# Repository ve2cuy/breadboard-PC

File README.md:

# breadboard-PC — an 8088 computer on a breadboard

A microcomputer with a PC/XT-inspired architecture, built on solderless breadboards around an
**Intel 8088**. Its ROM, whose source code is **written entirely in 8086 assembly language**, boots
into an interactive menu, runs two BASIC interpreters and **boots PC-DOS 2.1, MS-DOS 3.30, 5.0 and
6.22** from 160 KB to 1.44 MB floppy disk images.

A project by Alain Boudreault (VE2CUY), 2026. *[Version française](README_fr.md)*

<p align="center">
  <br>
  <em>The build: the Black Pill STM32F411 bridge (top centre), the 8088, the 8255, the 8259, the ROM and
  the RAM. The LCD shows the “Information” screen (date and time, versions, RAM, disk, speed).</em>
</p>

## Online simulator

The [Solution-02](Solution-02/) board (stand-alone 8088 / NEC V20, 512 KB, 20×4 LCD, LEDs, PS/2 keyboard,
software UART, SD card) also runs in the browser, emulated in Rust/WebAssembly with its real BIOS:
**[launch the simulator](https://ve2cuy.github.io/breadboard-PC/)** (English and French). PCB view with live pin levels, oscilloscope,
32-channel logic analyzer with protocol decoders, debugger, fault injection.

<p align="center">
  <br>
  <em>The simulator running PC-DOS 2.1 (DIR typed on the PS/2 keyboard). Click the animation to open the simulator.
  More in the <a href="Solution-02/Simulateur/README.md">simulator README</a>.</em>
</p>

**New: [the simulator with the Pico W](https://ve2cuy.github.io/breadboard-PC/pico/)** — the current board (2026-11-23):
- the ATmega328P terminal;
- a Raspberry Pi Pico W on ports 50h-57h behind two SN74LVC245, with READY wait states;
- BIOS 3.3, which reads the SD card through the Pico;
- **TCP/IP and the Internet** from DOS (mTCP) and ELKS, through the Pico's real firmware core: DNS-over-HTTPS, HTTP,
  and real TCP with a small local relay.

Details in the [Simulateur-Pico README](Solution-02/Simulateur-Pico/README.md) and the [Pico README](Solution-02/pico/README.md).

## At a glance

| | |
|---|---|
| **Processor** | Intel 8088, 4.77 MHz by default, adjustable from 1 to 10 MHz (tested up to 7.38 MHz) |
| **Memory** | 256 KB ROM (W29C020C, `C0000h`–`FFFFFh`); **512 KB** static RAM (AS6C4008, `00000h`–`7FFFFh`), 510 KB of it for DOS |
| **I/O** | 8255A in mode 2 (bus to the bridge), 8259A (interrupts), 4×20 I2C LCD, PS/2 keyboard |
| **Bridge** | WeAct **Black Pill STM32F411** board (firmware 1.6): keyboard, USB terminal, LCD, clock, disk, RESET |
| **Software** | ROM written entirely in assembly (NASM, strict 8086 instruction set): menu, BIOS for DOS, Tiny BASIC, GW-BASIC-style BASIC, RAM test with a memory map |
| **Operating systems** | PC-DOS 2.1, MS-DOS 3.30, 5.0 and 6.22, booted from a floppy disk image (160 KB to 1.44 MB) |

## The build

The core of the machine (processor, address latches, data buffer, ROM, RAM, decoding) is wired on
breadboards with 74LS/74HC logic and no programmable logic (no GAL, no CPLD):

- two **74LS373** latch `A0`–`A7` and `A16`–`A19` on `ALE`; a **74HC245** buffers `D0`–`D7`
  (`DEN`, `DT/R`);
- two **74LS00** do all the decoding, with `M` = memory cycle (`IO/M` = 0):
  - **ROM**: `CE# = NAND(A19, M)` — `C0000h`–`FFFFFh`;
  - **RAM**: `CE# = NAND(/A19, M)` — `00000h`–`7FFFFh`;
  - **8255** (ports `80h`–`83h`): `CS# = NAND(IO, A7)`;
  - **8259** (ports `20h`–`21h`): `CS# = NAND(IO, A5)`;
- the 8088's `RD#` and `WR#` go straight to the ROM, the RAM, the 8255 and the 8259.

<p align="center">
  <br>
  <em>Schematic of the build (KiCad, <a href="kicad/Breadboard-pc">kicad/Breadboard-pc</a>). The clock comes from the
  bridge (<code>CLK_STM</code>) or from an external input, selected by jumper JP1. On the PCB, a third 74LS373 (U12)
  also latches A8-A11, so the whole address bus (A0-A19) can drive two 10-LED bargraphs (readable when single-stepping or halted); J5 brings the bus
  out on a 2 x 20 header.</em>
</p>

<p align="center">
  <br>
  <em>PCB v2 (120 x 124.2 mm, 2 layers), KiCad 3D render: 8088, ZIF socket for the ROM, Black Pill bridge (U5),
  512 KB RAM, 8255, 8259, address bargraphs and J5 bus connector. Routed with Freerouting.</em>
</p>

### The signals in action

The animation follows the machine from RESET to DOS reading a sector: the reset vector fetched from
ROM, a RAM write, programming the 8259 and the interrupt vector table (IVT), a key press and the `IRQ1`
interrupt, a BIOS call (`INT 13h`) and the bridge's burst reply. For each step: the chips involved, the
level of the control signals and the memory area targeted.

The animation is generated by [medias/animation/generer_signaux.py](medias/animation/generer_signaux.py).

## The circuit

The 8088 does not bit-bang any peripheral. All traffic goes through **a single 8255 in mode 2**: an
8-bit bidirectional bus with hardware handshaking, connected to the bridge. Every byte received from
the bridge raises an interrupt (`IR1` of the 8259); during a bridge command, `IR1` is masked and the
BIOS polls for the replies.

```mermaid
flowchart LR
    CPU["Intel 8088"] --- BUS(("Bus<br>A0-A19 / D0-D7"))
    BUS --- ROM["256 KB ROM<br>W29C020C"]
    BUS --- RAM["512 KB RAM<br>AS6C4008"]
    BUS --- PIO["8255A<br>mode 2"]
    BUS --- PIC["8259A"]
    PIO -- "INTR → IR1" --> PIC
    PIC -- INTR --> CPU
    PIO <== "Port A (8 bits) + handshake" ==> BRIDGE["Bridge<br>Black Pill STM32F411"]
    BRIDGE -- "CLK, RESET" --> CPU
    KBD["PS/2 keyboard"] --> BRIDGE
    BRIDGE <-- "USB (serial + drive)" --> PC["PC: terminal"]
    BRIDGE --> LCD["4×20 I2C LCD"]
    BRIDGE --- FLASH["8 MB flash<br>FAT16"]
```

The bridge wiring in detail (pins, 3.3 V / 5 V levels, pull-up resistors) is described (in French) in
[arduino/8088_bridge_stm32/README.md](arduino/8088_bridge_stm32/README.md).

## The STM32 bridge

The bridge firmware (a PlatformIO project, [arduino/8088_bridge_stm32](arduino/8088_bridge_stm32))
gives the 8088 the peripherals of a PC:

| Function | Details |
|---|---|
| **PS/2 keyboard** | Frame decoding; raw scan codes passed to the 8088 |
| **Terminal** | Native USB serial port to the PC (ANSI, 80 columns, UTF-8) |
| **Display** | 4×20 HD44780 LCD over I2C (PCF8574) |
| **Real-time clock** | STM32 RTC (32.768 kHz crystal): `TIME$`, `DATE$`, `INT 1Ah` |
| **Disk** | 8 MB W25Q64 SPI flash formatted FAT16: files, sectors, floppy images mounted as A: (read-only ones too) |
| **Throughput** | Replies sent **in bursts**, as soon as the 8088 has read the previous byte (firmware 1.6) |
| **USB drive** | The flash is exposed to the PC as a USB drive (`USB ON` / `USB OFF`) to copy files onto it |
| **8088 clock** | `CLK` signal generated by hardware PWM, 1 to 10 MHz |
| **8088 RESET** | Held while the bridge starts up; **Ctrl-Alt-Del** (PS/2) or **Ctrl-\\** (terminal) |

The 8088 talks to the bridge through a command protocol on a dedicated channel
(see [Solution-01/lib/bridge.asm](Solution-01/lib/bridge.asm)). The firmware is flashed over USB, with
the board in DFU mode: `platformio run -e blackpill_f411ce_usbdrive -t upload`.

## The menu

At power-up, the ROM displays a menu on both the terminal and the LCD. It can be driven from either
the PS/2 keyboard or the terminal; **Esc** goes back to the previous menu.

| Menu | Options |
|---|---|
| **1) Basic** | Tiny BASIC; GW-BASIC-style BASIC |
| **2) Memory functions** | Memory dump and editing, CPU registers, code entry and execution, interrupt vector table; **RAM test**: *Trace* (full progress), *MAP* (memory map and summary only) or *Loop* (MAP repeated until Esc) |
| **3) USB Disk** | USB drive toggle, file list, **booting a disk image** |
| **4) Configuration** | Clock speed (0.1 and 1 MHz steps; 2.35, 4.77, 8 and 7.2 MHz presets), CPU speed test, date and time, information screen |

The **RAM test** checks all 512 KB byte by byte (the test stack is moved to low RAM, the last 2 KB are
tested separately), then the address lines `A0`–`A18` (the chip's real capacity). It ends with a
**memory map** (one character per KB) and the good and faulty amounts.

## BASIC

An original reimplementation inspired by GW-BASIC: same keywords, same error messages, integers,
single-precision floating point (in software) and strings. About 54 KB are free for programs.

| Category | Commands and functions |
|---|---|
| **Program** | `RUN` `LIST` `EDIT` `DELETE` `NEW` `CLEAR` `CONT` `TRON` `TROFF` `HELP` `SYSTEM` |
| **Control flow** | `IF…THEN…ELSE` `GOTO` `GOSUB`/`RETURN` `ON…GOTO/GOSUB` `FOR…NEXT` `WHILE…WEND` `END` `STOP` |
| **Data** | `LET` `DIM` `ERASE` `SWAP` `DATA`/`READ`/`RESTORE` `DEF FN` `DEFINT`/`DEFSNG`/`DEFSTR` |
| **Input/output** | `PRINT` `INPUT` `LINE INPUT` `INKEY$` `CLS` `LOCATE` `COLOR` `BEEP` |
| **Math** | `ABS` `SGN` `INT` `FIX` `SQR` `SIN` `COS` `TAN` `ATN` `LOG` `EXP` `RND` `RANDOMIZE` |
| **Strings** | `LEN` `LEFT$` `RIGHT$` `MID$` `INSTR` `CHR$` `ASC` `STR$` `VAL` `HEX$` `UCASE$` `STRING$` |
| **Files** | `SAVE` `LOAD` `MERGE` `FILES` `KILL` `FORMAT`; `OPEN` `PRINT #` `INPUT #` `EOF` `CLOSE` |
| **Clock** | `TIMER` `TIME$` `DATE$` (read and set the bridge RTC) |
| **Machine** | `PEEK` `POKE` `DEF SEG` `INP` `OUT` `WAIT` `CALL` `FRE` |
| **Disk and system** | `DSKREAD` `DSKWRITE` `USB ON`/`OFF` `BOOT "image.img"` |

## DOS 2.1 to 6.22

The ROM provides the BIOS layer a DOS expects: disk (`INT 13h`, CHS and LBA), keyboard (`INT 16h`),
clock (`INT 1Ah`), text output to the terminal (`INT 10h`) and bootstrap (`INT 19h`). A floppy image
copied to the flash (through the USB drive) is mounted as drive **A:** and booted from
**USB Disk → 3) Boot disk image**, or with `BOOT "PCDOS2_1.IMG"` from BASIC. DOS writes go to the
image file; a read-only image is mounted anyway, without write access.

<p align="center">
  <br>
  <em>PC-DOS 2.1: booting from the image (one dot per sector read), VER, DIR /W</em>
</p>

<p align="center">
  <br>
  <em>MS-DOS 3.30</em>
</p>

What makes DOS 5.0 and 6.22 possible:

- **512 KB of RAM** (these versions require at least 256 KB);
- the **model byte** `FEh` (PC/XT) at `F000:FFFE`: without it, DOS 5 takes the AT keyboard path
  (ports `60h`/`64h`), which hits the 8259 with this decoding;
- the BIOS tick counter `0040:006C`, kept in step with the bridge clock (there is no timer on this
  build): DOS 6 times its F5/F8 boot pause with it;
- **1.44 MB** floppies (geometry from the image size, `INT 13h AH=08h/18h`).

DOS accented letters and box-drawing characters (code page 437) are converted to **UTF-8** on the
terminal: the PC terminal must be set to UTF-8.

Limitations: no video hardware (programs that write to video memory display nothing); DOS keyboard
input from the terminal only; **KEYB** does not work (it reads the keyboard through port `60h`) —
setup disks that start it from `AUTOEXEC.BAT` must have it removed (see the `-nokeyb` copies in
[PC-DOS/](PC-DOS)).

## Building the ROM

```sh
cd Solution-01
make            # solution-01.bin (256 KB, 512 KB RAM); make rom-en for English; make rom-128: 128 KB RAM
make check      # checks size, reset vector, signature and model byte
make test       # test benches under emulation (Unicorn)
make test-rom   # full ROM simulation: DOS, BASIC, PS/2 keyboard
```

Tools: NASM, GNU Make, Python 3 (+ `unicorn` for the tests); PlatformIO for the bridge.

## Repository layout

| Folder | Contents |
|---|---|
| [Solution-01/](Solution-01) | 8088 ROM (NASM) and tests; full technical documentation (in French) in [Solution-01/README.md](Solution-01/README.md) |
| [arduino/8088_bridge_stm32/](arduino/8088_bridge_stm32) | Firmware of the Black Pill STM32F411 bridge (PlatformIO) |
| [kicad/](kicad) | Schematic and PCB of the build |
| [PC-DOS/](PC-DOS) | Test floppy disk images |
| [medias/](medias) | Datasheets, schematic, PCB render, signal animation and screenshots |

> The terminal screenshots on this page are produced by the actual (English) ROM, running in the
> project's simulator ([medias/captures/generer.py](medias/captures/generer.py)).

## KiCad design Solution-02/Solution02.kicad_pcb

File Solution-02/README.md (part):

# Solution-02 — stand-alone 8088 / NEC V20 computer (VE2CUY)

*[Version française](README_fr.md)*

An 8088 (or NEC V20) computer built on a breadboard, **without the STM32 bridge**:
the processor drives its LCD and its memory directly.

- Clock: 82C84 + 16 MHz crystal → **5.33 MHz** (16 / 3)
- ROM: 29C020 (W29C020C), 256 KB
- RAM: HM628512, 512 KB
- Address latches: 2 × 74HC573 (U2: A0–A7, U3: A16–A19)
- Decoding: 74LS00 (U5), 74LS138 (U8), 74LS02 (U9)
- Display: 20×4 LCD (HD44780 / ST7066U), 8-bit bus, write only
- Parallel I/O: 8255 (U7, µPD71055C) at 10h–13h, 24 LEDs on J1–J3
- Keyboard and UART: second 8255 (U12) at 30h–33h — PS/2 keyboard (USB-A socket J4) and
  9600 8N1 software UART (J5), bit-banged as in Solution-01
- **PC-DOS 2.1 in ROM**: the 180 KB floppy is in the ROM (drive A:, read only); IBM PC-style
  BIOS (INT 10h, 13h, 16h…) through software interrupts, 24 × 80 DOS screen seen through a
  20 × 4 window on the LCD

Schematic: [Solution02.kicad_sch](Solution02.kicad_sch).
PCB: [Solution02.kicad_pcb](Solution02.kicad_pcb) (172 × 100 mm, 2 layers; see [PCB](#pcb)).
Log of the steps: [Directives.md](Directives.md) (French).

<p align="center">
  <br>
  <em>Solution-02 schematic (click to enlarge).</em>
</p>

## Memory map

| Addresses | Contents | Selection |
|---|---|---|
| 00000h–7FFFFh | 512 KB RAM | CE# = NAND(/A19, M) — U5 pin 8 |
| 80000h–FFFFFh | 256 KB ROM | CE# = NAND(A19, M) — U5 pin 6 |

A18 is not connected to the ROM: the 256 KB image appears twice
(80000h–BFFFFh and C0000h–FFFFFh). The BIOS occupies the last 64 KB of the
image (offset 30000h), seen at **F000:0000**. At reset, the 8088 starts
at FFFF:0000 = FFFF0h = F000:FFF0 (offset 3FFF0h of the image), where there is
a `JMP F000:0000`.

ROM and RAM contents with BIOS 2.3:

| Addresses | Contents |
|---|---|
| 00000h–003FFh | interrupt vector table (filled by "Load DOS") |
| 00400h–004FFh | BIOS data area (BDA): equipment, memory, video mode |
| 00500h–5EBFFh | DOS and programs (**379 KB** reported by INT 12h; **507 KB** when B: is the card's DOS 2.1 image) |
| 5EC00h–5EFFFh | private INT 10h stack (1 KB, BIOS 2.5; at 7EC00h–7EFFFh when DOS gets 507 KB) |
| 10000h–1FFFFh | (outside DOS) **BASIC** segment (menu 6): program, variables, stack |
| 5F000h–7EFFFh | **drive B:**: 128 KB virtual disk (kept after Ctrl + Alt + Del) |
| 7F000h–7FFFFh | BIOS data (DSEG = 7F00h): 24 × 80 screen, variables, queues, LCD copy, animation stack (900h–AFFh), menu stack |
| C0000h–ECFFFh | **reduced PC-DOS 2.1 floppy** (180 KB: 40 cylinders, 1 head, 9 sectors) = offset 0 of the image |
| ED000h–EFFFFh | free (FFh) |
| F0000h–F7FFFh | BIOS |
| F8000h–FFFEFh | **BASIC** (basic_s02.asm: the Solution-01 BASIC, ~25 KB) |
| FFFF0h | RESET |

The ROM's PGM (WE#) pin is tied to +5 V: a write by DOS or a program into the
ROM area (for instance at B8000h, a PC's video memory) has no effect.

## I/O ports (74LS138, U8)

U8 decodes **A7 = 0**, **IO/M = 1** (E1# = E2# = A7, E3 = IO/M) and
**A6–A4** (inputs A, B, C). Each active-low output covers a block of 16 ports:

| Output | U8 pin | Ports | Use |
|---|---|---|---|
| O0 | 15 | 00h–0Fh | **LCD (in use)**: 00h = command, 01h = data (RS = A0) |
| O1 | 14 | 10h–1Fh | **8255 (U7, in use)**: 10h = PA, 11h = PB, 12h = PC, 13h = control (A0–A1) |
| O2 | 13 | 20h–2Fh | **8259A (U13)**: 20h = ICW1/OCW2/OCW3 (A0 = 0), 21h = ICW2-4/OCW1 (mask) — as on the PC |
| O3 | 12 | 30h–3Fh | **second 8255 (U12, in use)**: 30h = PA, 31h = PB, 32h = PC, 33h = control (keyboard, software UART, SD reader) |
| O4 | 11 | 40h–4Fh | **8253-2 (U15)**: 40h–42h = counters 0–2, 43h = mode (A0–A1) |
| O5 | 10 | 50h–5Fh | free |
| O6 | 9 | 60h–6Fh | **port 61h latch (U16)**: bit 0 = GATE2, bit 1 = speaker (write only) |
| O7 | 7 | 70h–7Fh | free |

Good to know:

- **A0–A3 do not go through the 138.** They go directly to the peripheral to
  select its registers. A peripheral that only uses a few of them, such as an
  8255 (A0–A1), appears several times in its block: 60h–63h, then 64h–67h, etc.
- **A8–A15 are not decoded.** With `IN/OUT port, AL` (8-bit port), they are 0.
  With `IN/OUT DX`, each block repeats every 256 ports.
- **Ports 80h–FFh (A7 = 1) are not decoded.** A second 138 enabled by A7 = 1
  and IO/M = 1 would provide 8 more blocks.
- **No RD#/WR# in the 138.** Its outputs depend only on the address. They suit
  as is the CS# of chips that receive RD# and WR# separately (8255, 8253, 8259,
  16550…). For a simple latch (74LS374/573) or a buffer (74LS244), the output
  must be combined with WR# or RD#, as for the LCD: E = NOR(WR#, O0) (U9), and
  the port 61h latch: clock = OR(WR#, O6) (U9). All 4 NOR gates of U9 are used.
- The decoding falls on the same blocks as a PC/XT: an 8259 on O2, an 8253 on
  O4 and an 8255 on O6 would be at the standard addresses (20h, 40h, 60h),
  which will make a compatible BIOS easier.

## 20×4 LCD

- Data bus DB0–DB7 connected directly to AD0–AD7 of the 8088.
- RS = A0 (latched by U2), E = NOR(WR#, O0) (U9 pin 13).
- R/W tied to ground: the busy flag cannot be read, each write is followed by
  a software delay.
- Contrast set by RV1 (VO pin).
- The E pulse lasts about 2 cycles (≈ 375 ns at 5.33 MHz): enough for an
  HD44780U (230 ns minimum), to watch with a slower controller.

## 8255 (U7) and LEDs

CMOS 8255 (µPD71055C) selected by **O1** of the 74LS138: ports **10h–13h**
(repeated up to 1Fh, since only A0–A1 go to the 8255).

| 8255 pin | Signal | Comes from |
|---|---|---|
| 34, 33, 32, 31, 30, 29, 28, 27 | D0–D7 | AD0–AD7 of the 8088 |
| 9, 8 | A0, A1 | U2 (74HC573) Q0, Q1 |
| 6 | CS# | U8 (74LS138) pin 14 (O1) |
| 5 | RD# | RD# (8088 pin 32) |
| 36 | WR# | WR# (8088 pin 29) |
| 35 | RESET | 82C84 RESET (U11 pin 10, 8088 pin 21) |
| 26 / 7 | VCC / GND | +5 V / GND (+ 100 nF) |
| 4, 3, 2, 1, 40, 39, 38, 37 | PA0–PA7 | J1 pins 1–8 |
| 18–25 | PB0–PB7 | J2 pins 1–8 |
| 14, 15, 16, 17, 13, 12, 11, 10 | PC0–PC7 | J3 pins 1–8 |

J1, J2 and J3 (1×10): pins 1–8 = PA/PB/PC 0–7, pin 9 = +5 V, pin 10 = GND.

LEDs: an output at 1 lights the LED if it is wired **output → 1 kΩ → anode,
cathode → GND** (pin 10). The 82C55 only supplies ~2.5 mA per output: for
brighter LEDs, go through a ULN2803 or a 74HC245.

**Bar graphs** (as in Solution-01): three HDSP-4830 (BAR1–BAR3) in parallel
with J1–J3, wired as a **contiguous chain of 30 LEDs**, like the address lines
of Solution-01: anode on the 8255 output, cathode to ground through **390 Ω** —
segments 1 to 9 through a network of 9 bussed resistors (RN1–RN3, SIP10),
segment 10 through a single resistor (R5–R7).

| Bar graph | Anode pins 1 → 10 | Cathodes |
|---|---|---|
| BAR1 | 1–6 free (bits 24–29), 7–10 = PC7 → PC4 | RN1 + R5 |
| BAR2 | PC3 → PC0, PA7 → PA2 | RN2 + R6 |
| BAR3 | PA1, PA0, PB7 → PB0 | RN3 + R7 |

Bit 0 (PB0) = pin 10 of BAR3, bit 23 (PC7) = pin 7 of BAR1: laid out from left
to right (BAR1, BAR2, BAR3, pin 1 on the left), the bar graphs show the BIOS
row (PC7 … PB0) with the 6 most significant LEDs off on the left. The current
is limited by the 82C55 output (~2.5 mA) rather than by the 390 Ω.

At RESET, the 8255 sets its 3 ports as inputs (floating outputs). The BIOS
sends control word **80h** (mode 0, PA, PB and PC as outputs) and turns the
LEDs off right at startup, just after initializing the LCD.

## 8253 (U15): timer

**NEC D8253C-2** (clock up to **5 MHz**) selected by **O4** of the 74LS138:
ports **40h–43h**, as on the PC (repeated up to 4Fh). The clock is PCLK of the
82C84 (16 MHz / 6 = **2.67 MHz**): an 8253-2 (5 MHz) or an 8254 (8 MHz) is
required; an ordinary 8253 or 8253-5 is limited to 2.6 MHz. In the schematic,
the symbol is the 82C54's (same pinout). The BIOS only uses what all these
chips have: mode 3 and counter latch (word 00h).

| 8253 pin | Signal | Comes from / goes to |
|---|---|---|
| 8 → 1 | D0 → D7 | AD0–AD7 of the 8088 |
| 19, 20 | A0, A1 | U2 (74HC573) Q0, Q1 |
| 21 | CS# | U8 (74LS138) pin 11 (O4) |
| 22 / 23 | RD# / WR# | 8088 pins 32 / 29 |
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
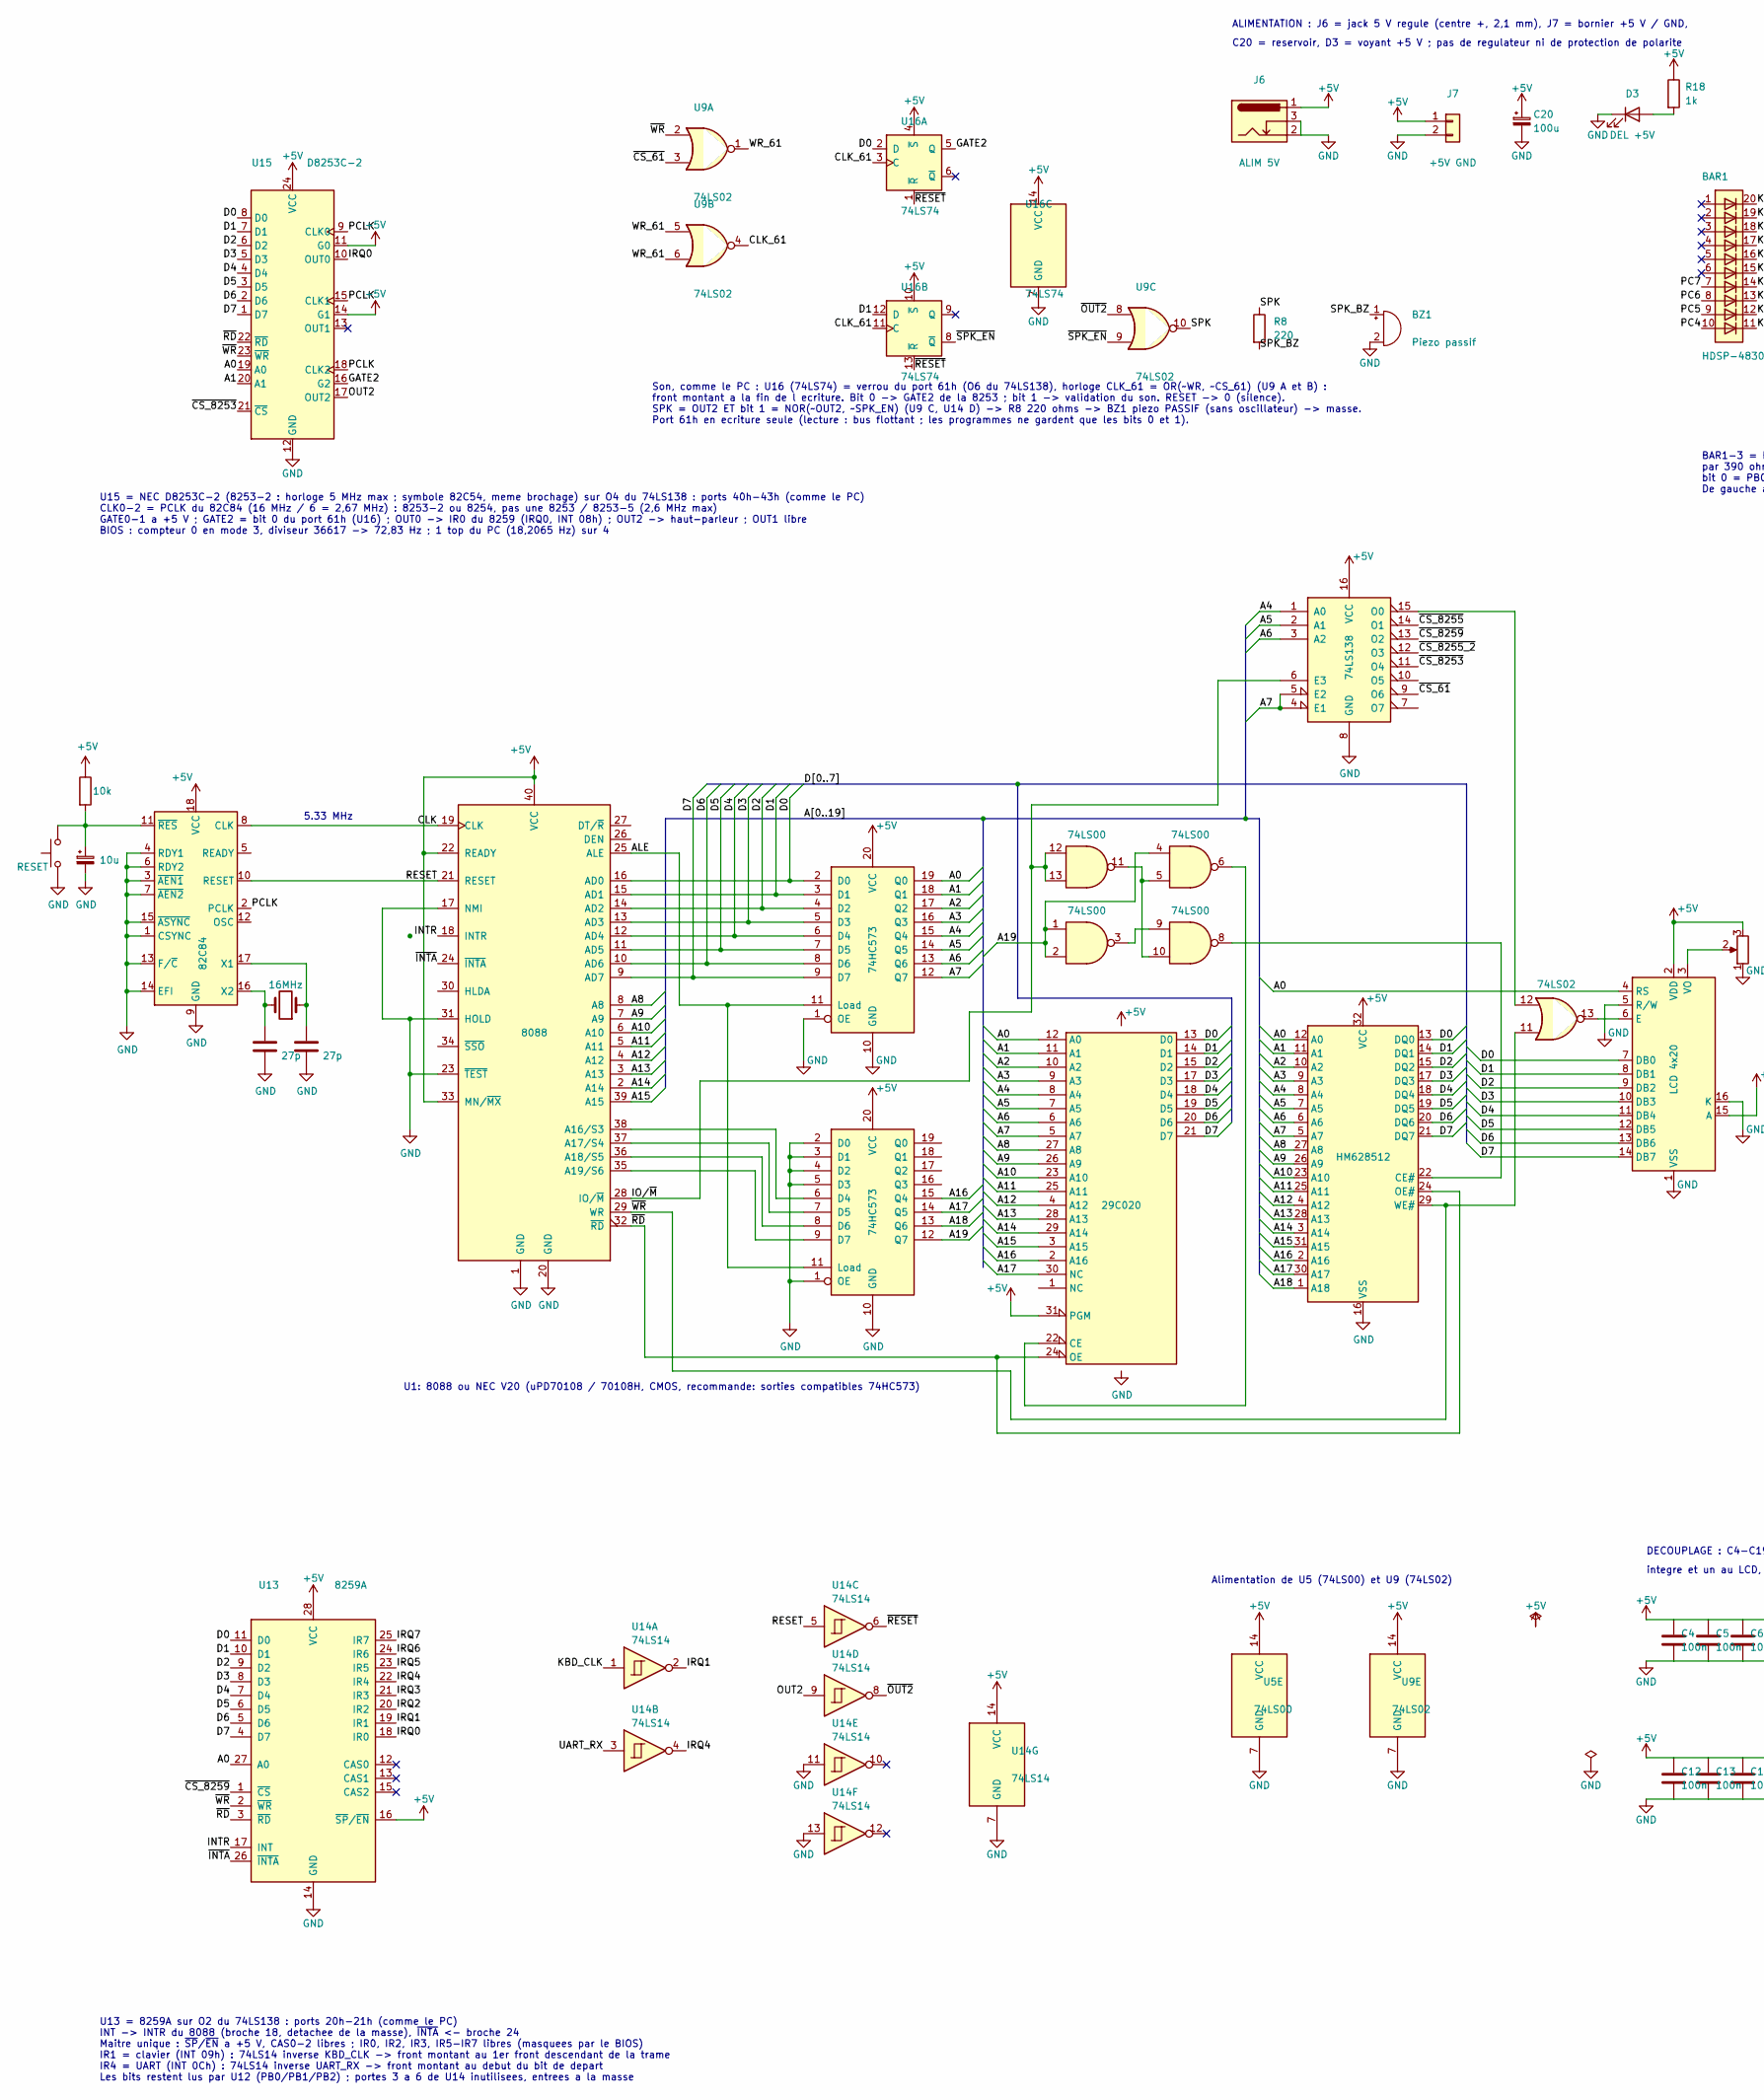
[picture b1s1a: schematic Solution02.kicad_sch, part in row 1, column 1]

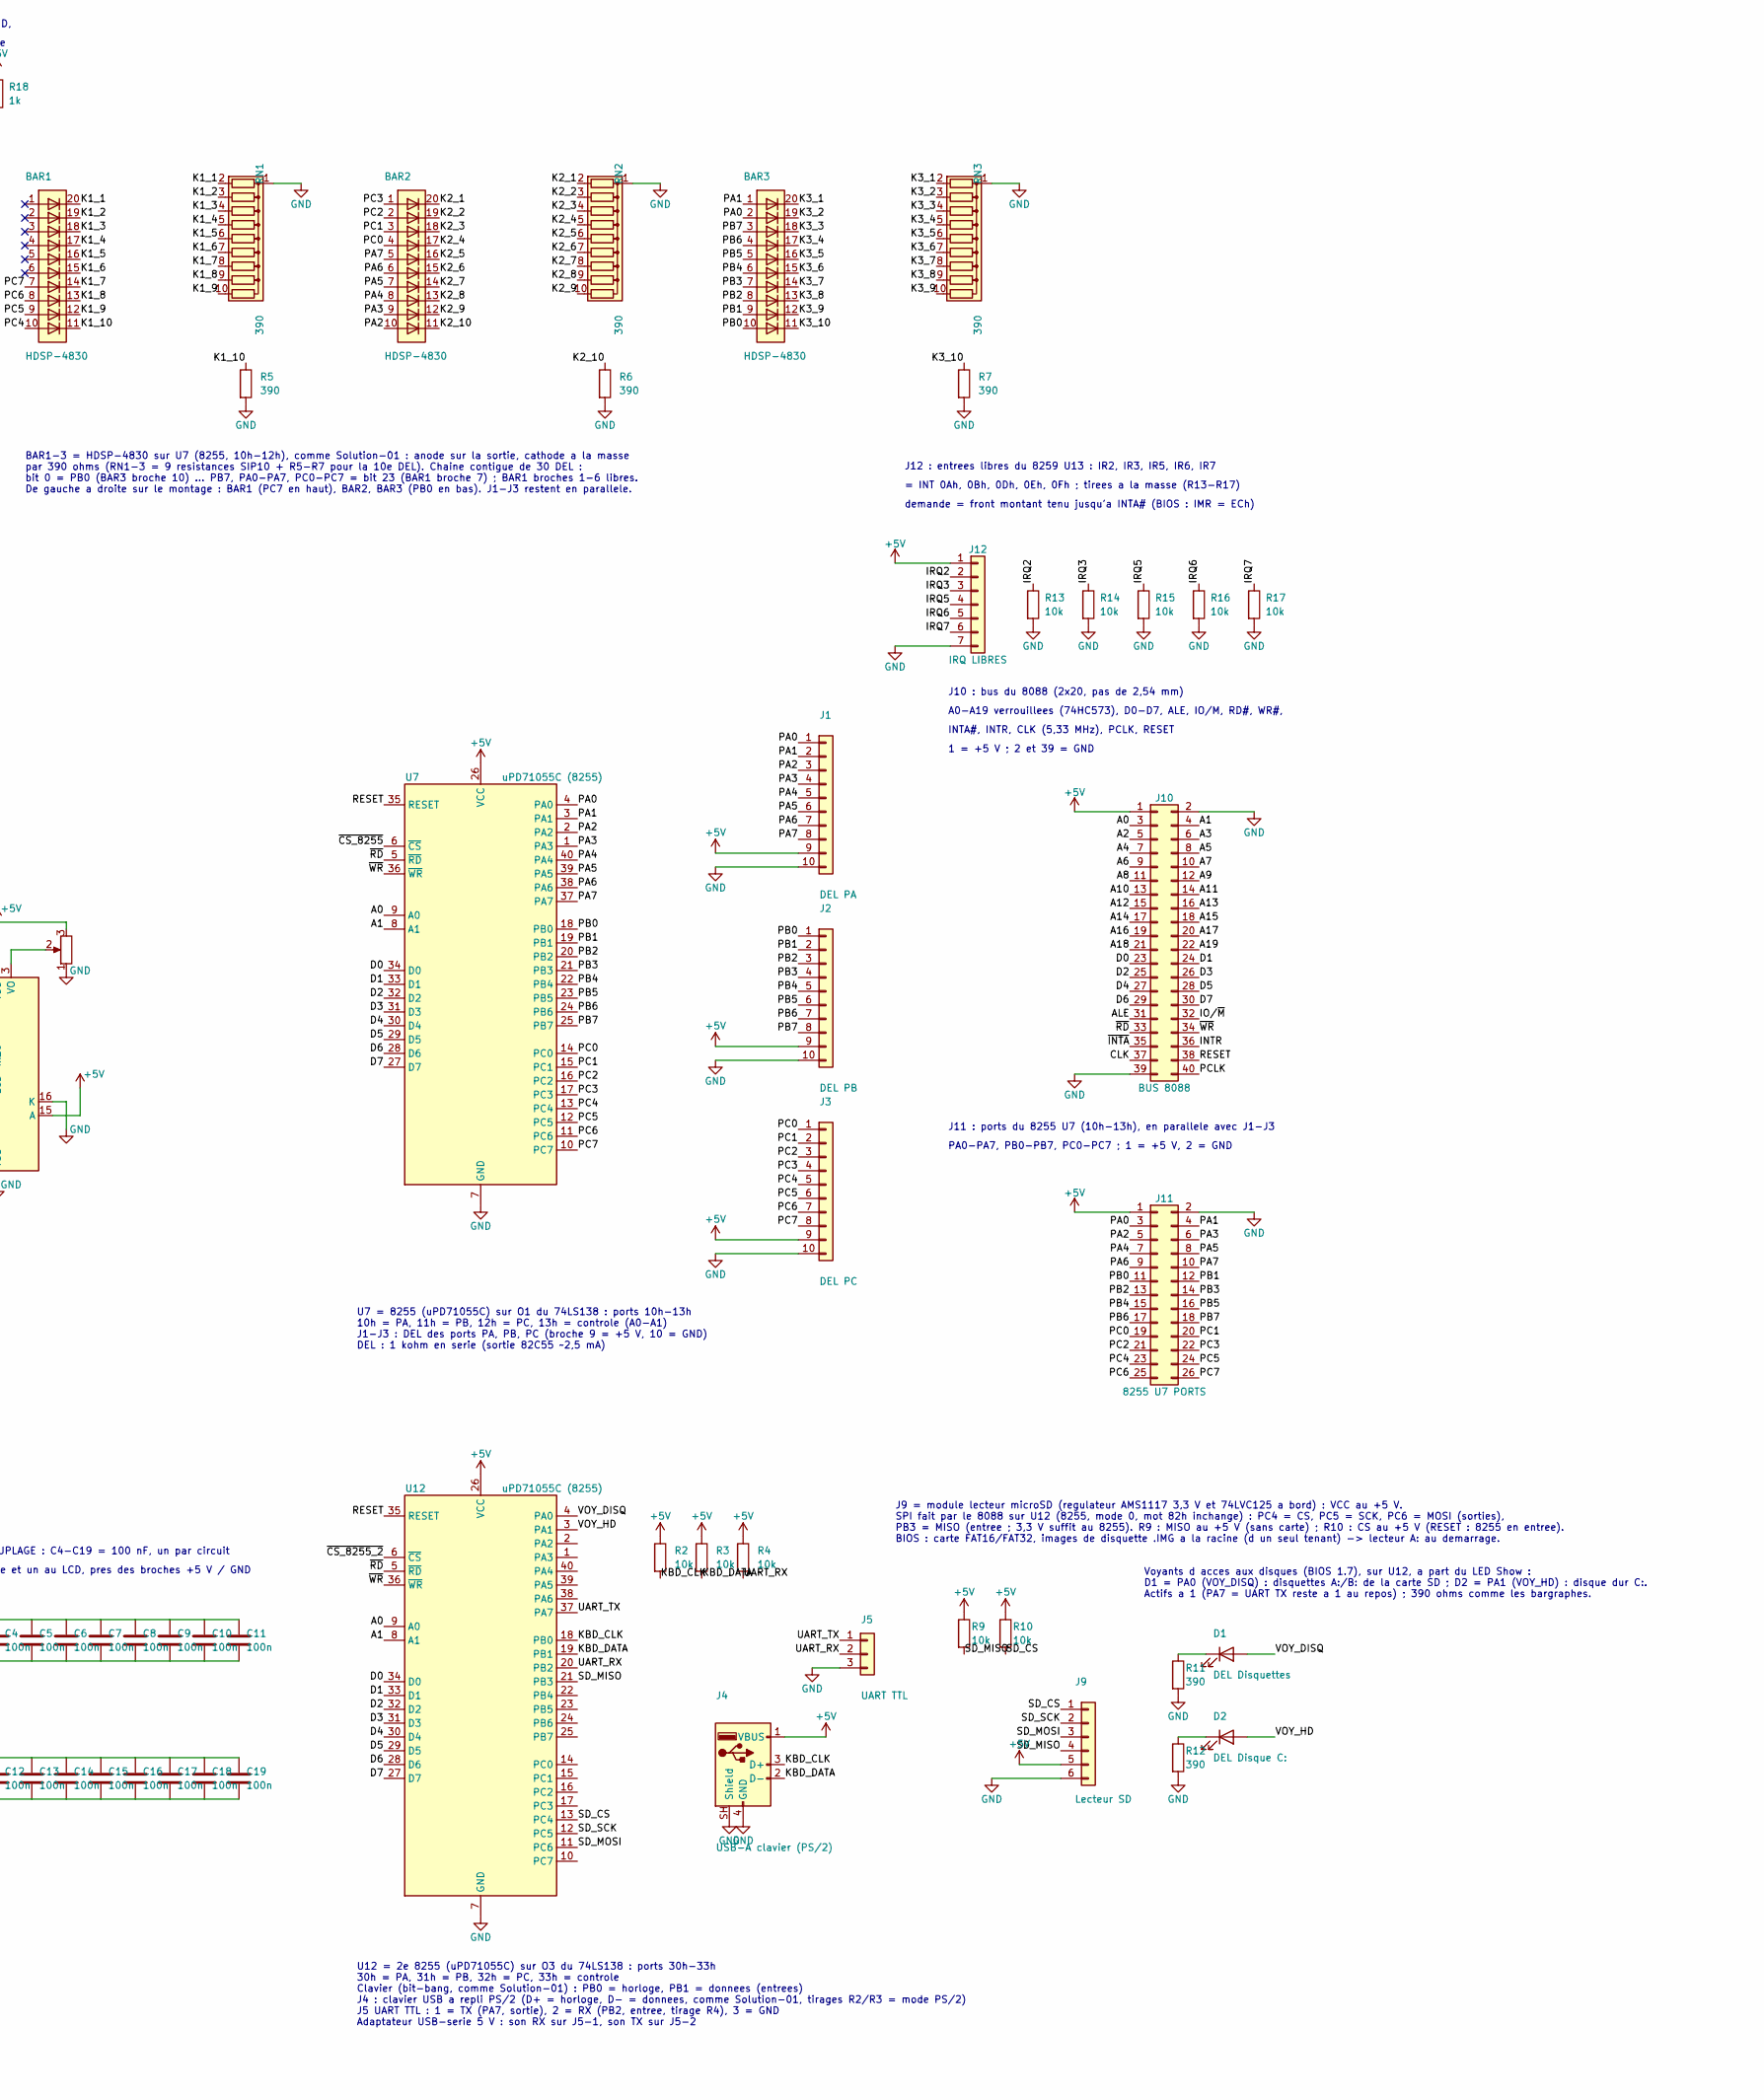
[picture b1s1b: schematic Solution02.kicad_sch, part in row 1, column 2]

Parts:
BAR1, BAR2, BAR3: HDSP-4830
BZ1: Piezo passif; Buzzer_12x9.5RM7.6
C1: 10u; CP_Radial_D5.0mm_P2.50mm
C2, C3: 27p; C_Disc_D5.0mm_W2.5mm_P5.00mm
C4, C5, C6, C7, C8, C9, C10, C11, C12, C13, C14, C15, C16, C17, C18, C19: 100n; C_Disc_D5.0mm_W2.5mm_P5.00mm
C20: 100u; CP_Radial_D6.3mm_P2.50mm
D1: DEL Disquettes; LED_D3.0mm
D2: DEL Disque C:; LED_D3.0mm
D3: DEL +5V; LED_D3.0mm
J1: DEL PA; PinHeader_1x10_P2.54mm_Vertical
J2: DEL PB; PinHeader_1x10_P2.54mm_Vertical
J3: DEL PC; PinHeader_1x10_P2.54mm_Vertical
J4: USB-A clavier (PS/2); USB_A_Molex_67643_Horizontal
J5: UART TTL; PinHeader_1x03_P2.54mm_Vertical
J6: ALIM 5V; BarrelJack_Horizontal
J7: +5V GND; PinHeader_1x02_P2.54mm_Vertical
J9: Lecteur SD; PinHeader_1x06_P2.54mm_Vertical
J10: BUS 8088; PinHeader_2x20_P2.54mm_Vertical
J11: 8255 U7 PORTS; PinHeader_2x13_P2.54mm_Vertical
J12: IRQ LIBRES; PinHeader_1x07_P2.54mm_Vertical
R1, R9, R10, R13, R14, R15, R16, R17: 10k; R_Axial_DIN0207_L6.3mm_D2.5mm_P7.62mm_Horizontal
R2, R3, R4: 10k; R_Axial_DIN0207_L6.3mm_D2.5mm_P10.16mm_Horizontal
R5, R6, R7, R11, R12: 390; R_Axial_DIN0207_L6.3mm_D2.5mm_P7.62mm_Horizontal
R8: 220; R_Axial_DIN0207_L6.3mm_D2.5mm_P7.62mm_Horizontal
R18: 1k; R_Axial_DIN0207_L6.3mm_D2.5mm_P7.62mm_Horizontal
RN1, RN2, RN3: 390; R_Array_SIP10
RV1: R_Potentiometer; Potentiometer_Bourns_3386P_Vertical
SW1: RESET; SW_PUSH_6mm
U1: 8088; DIP-40_W15.24mm
U2, U3: 74HC573; DIP-20_W7.62mm
U4: 29C020; DIP_Socket-32_W11.9mm_W12.7mm_W15.24mm_W17.78mm_W18.5mm_3M_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
U5: 74LS00; DIP-14_W7.62mm
U6: HM628512; DIP-32_W15.24mm
U7, U12: uPD71055C (8255); DIP-40_W15.24mm
U8: 74LS138; DIP-16_W7.62mm
U9: 74LS02
U10: LCD 4x20; LCD_2004A
U11: 82C84; DIP-18_W7.62mm
U13: 8259A; DIP-28_W15.24mm
U14: 74LS14; DIP-14_W7.62mm
U15: D8253C-2; DIP-24_W15.24mm
U16: 74LS74; DIP-14_W7.62mm
Y1: 16MHz; Crystal_HC49-4H_Vertical

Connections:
+5V: C4.1, C5.1, C6.1, C7.1, C8.1, C9.1, C10.1, C11.1, C12.1, C13.1, C14.1, C15.1, C16.1, C17.1, C18.1, C19.1, C20.1, J1.9, J2.9, J3.9, J4.1 (VBUS), J6.1, J7.1, J9.5, J10.1, J11.1, J12.1, R1.1, R2.1, R3.1, R4.1, R9.1, R10.1, R18.1, RV1.3, U1.22 (READY), U1.33 (MN/~MX), U1.40 (VCC), U2.20 (VCC), U3.20 (VCC), U4.31 (PGM), U4.32 (VCC), U5.14 (VCC), U6.32 (VCC), U7.26 (VCC), U8.16 (VCC), U9.14 (VCC), U10.2 (VDD), U10.15 (A), U11.18 (VCC), U12.26 (VCC), U13.16 (~SP/~EN), U13.28 (VCC), U14.14 (VCC), U15.11 (G0), U15.14 (G1), U15.24 (VCC), U16.4 (~S), U16.10 (~S), U16.14 (VCC)
/A0: J10.3, U2.19 (Q0), U4.12 (A0), U6.12 (A0), U7.9 (A0), U10.4 (RS), U12.9 (A0), U13.27 (A0), U15.19 (A0)
/A1: J10.4, U2.18 (Q1), U4.11 (A1), U6.11 (A1), U7.8 (A1), U12.8 (A1), U15.20 (A1)
/A2: J10.5, U2.17 (Q2), U4.10 (A2), U6.10 (A2)
/A3: J10.6, U2.16 (Q3), U4.9 (A3), U6.9 (A3)
/A4: J10.7, U2.15 (Q4), U4.8 (A4), U6.8 (A4), U8.1 (A0)
/A5: J10.8, U2.14 (Q5), U4.7 (A5), U6.7 (A5), U8.2 (A1)
/A6: J10.9, U2.13 (Q6), U4.6 (A6), U6.6 (A6), U8.3 (A2)
/A7: J10.10, U2.12 (Q7), U4.5 (A7), U6.5 (A7), U8.4 (E1), U8.5 (E2)
/A8: J10.11, U1.8 (A8), U4.27 (A8), U6.27 (A8)
/A9: J10.12, U1.7 (A9), U4.26 (A9), U6.26 (A9)
/A10: J10.13, U1.6 (A10), U4.23 (A10), U6.23 (A10)
/A11: J10.14, U1.5 (A11), U4.25 (A11), U6.25 (A11)
/A12: J10.15, U1.4 (A12), U4.4 (A12), U6.4 (A12)
/A13: J10.16, U1.3 (A13), U4.28 (A13), U6.28 (A13)
/A14: J10.17, U1.2 (A14), U4.29 (A14), U6.3 (A14)
/A15: J10.18, U1.39 (A15), U4.3 (A15), U6.31 (A15)
/A16: J10.19, U3.15 (Q4), U4.2 (A16), U6.2 (A16)
/A17: J10.20, U3.14 (Q5), U4.30 (NC), U6.30 (A17)
/A18: J10.21, U3.13 (Q6), U6.1 (A18)
/A19: J10.22, U3.12 (Q7), U5.1, U5.2, U5.4
/ALE: J10.31, U1.25 (ALE), U2.11 (Load), U3.11 (Load)
/CLK: J10.37, U1.19 (CLK), U11.8 (CLK)
/CLK_61: U9.4, U16.3 (C), U16.11 (C)
/D0: J10.23, U1.16 (AD0), U2.2 (D0), U4.13 (D0), U6.13 (DQ0), U7.34 (D0), U10.7 (DB0), U12.34 (D0), U13.11 (D0), U15.8 (D0), U16.2 (D)
/D1: J10.24, U1.15 (AD1), U2.3 (D1), U4.14 (D1), U6.14 (DQ1), U7.33 (D1), U10.8 (DB1), U12.33 (D1), U13.10 (D1), U15.7 (D1), U16.12 (D)
/D2: J10.25, U1.14 (AD2), U2.4 (D2), U4.15 (D2), U6.15 (DQ2), U7.32 (D2), U10.9 (DB2), U12.32 (D2), U13.9 (D2), U15.6 (D2)
/D3: J10.26, U1.13 (AD3), U2.5 (D3), U4.17 (D3), U6.17 (DQ3), U7.31 (D3), U10.10 (DB3), U12.31 (D3), U13.8 (D3), U15.5 (D3)
/D4: J10.27, U1.12 (AD4), U2.6 (D4), U4.18 (D4), U6.18 (DQ4), U7.30 (D4), U10.11 (DB4), U12.30 (D4), U13.7 (D4), U15.4 (D4)
/D5: J10.28, U1.11 (AD5), U2.7 (D5), U4.19 (D5), U6.19 (DQ5), U7.29 (D5), U10.12 (DB5), U12.29 (D5), U13.6 (D5), U15.3 (D5)
/D6: J10.29, U1.10 (AD6), U2.8 (D6), U4.20 (D6), U6.20 (DQ6), U7.28 (D6), U10.13 (DB6), U12.28 (D6), U13.5 (D6), U15.2 (D6)
/D7: J10.30, U1.9 (AD7), U2.9 (D7), U4.21 (D7), U6.21 (DQ7), U7.27 (D7), U10.14 (DB7), U12.27 (D7), U13.4 (D7), U15.1 (D7)
/GATE2: U15.16 (G2), U16.5 (Q)
/INTR: J10.36, U1.18 (INTR), U13.17 (INT)
/IO/~M: J10.32, U1.28 (IO/~M), U5.12, U5.13, U8.6 (E3)
/IRQ0: U13.18 (IR0), U15.10 (OUT0)
/IRQ1: U13.19 (IR1), U14.2
/IRQ2: J12.2, R13.1, U13.20 (IR2)
/IRQ3: J12.3, R14.1, U13.21 (IR3)
/IRQ4: U13.22 (IR4), U14.4
/IRQ5: J12.4, R15.1, U13.23 (IR5)
/IRQ6: J12.5, R16.1, U13.24 (IR6)
/IRQ7: J12.6, R17.1, U13.25 (IR7)
/K1_1: BAR1.20 (K), RN1.2 (R1)
/K1_2: BAR1.19 (K), RN1.3 (R2)
/K1_3: BAR1.18 (K), RN1.4 (R3)
/K1_4: BAR1.17 (K), RN1.5 (R4)
/K1_5: BAR1.16 (K), RN1.6 (R5)
/K1_6: BAR1.15 (K), RN1.7 (R6)
/K1_7: BAR1.14 (K), RN1.8 (R7)
/K1_8: BAR1.13 (K), RN1.9 (R8)
/K1_9: BAR1.12 (K), RN1.10 (R9)
/K1_10: BAR1.11 (K), R5.1
/K2_1: BAR2.20 (K), RN2.2 (R1)
/K2_2: BAR2.19 (K), RN2.3 (R2)
/K2_3: BAR2.18 (K), RN2.4 (R3)
/K2_4: BAR2.17 (K), RN2.5 (R4)
/K2_5: BAR2.16 (K), RN2.6 (R5)
/K2_6: BAR2.15 (K), RN2.7 (R6)
/K2_7: BAR2.14 (K), RN2.8 (R7)
/K2_8: BAR2.13 (K), RN2.9 (R8)
/K2_9: BAR2.12 (K), RN2.10 (R9)
/K2_10: BAR2.11 (K), R6.1
/K3_1: BAR3.20 (K), RN3.2 (R1)
/K3_2: BAR3.19 (K), RN3.3 (R2)
/K3_3: BAR3.18 (K), RN3.4 (R3)
/K3_4: BAR3.17 (K), RN3.5 (R4)
/K3_5: BAR3.16 (K), RN3.6 (R5)
/K3_6: BAR3.15 (K), RN3.7 (R6)
/K3_7: BAR3.14 (K), RN3.8 (R7)
/K3_8: BAR3.13 (K), RN3.9 (R8)
/K3_9: BAR3.12 (K), RN3.10 (R9)
/K3_10: BAR3.11 (K), R7.1
/KBD_CLK: J4.3 (D+), R2.2, U12.18 (PB0), U14.1
/KBD_DATA: J4.2 (D-), R3.2, U12.19 (PB1)
/OUT2: U14.9, U15.17 (OUT2)
/PA0: BAR3.2 (A), J1.1, J11.3, U7.4 (PA0)
/PA1: BAR3.1 (A), J1.2, J11.4, U7.3 (PA1)
/PA2: BAR2.10 (A), J1.3, J11.5, U7.2 (PA2)
/PA3: BAR2.9 (A), J1.4, J11.6, U7.1 (PA3)
/PA4: BAR2.8 (A), J1.5, J11.7, U7.40 (PA4)
/PA5: BAR2.7 (A), J1.6, J11.8, U7.39 (PA5)
/PA6: BAR2.6 (A), J1.7, J11.9, U7.38 (PA6)
/PA7: BAR2.5 (A), J1.8, J11.10, U7.37 (PA7)
/PB0: BAR3.10 (A), J2.1, J11.11, U7.18 (PB0)
/PB1: BAR3.9 (A), J2.2, J11.12, U7.19 (PB1)
/PB2: BAR3.8 (A), J2.3, J11.13, U7.20 (PB2)
/PB3: BAR3.7 (A), J2.4, J11.14, U7.21 (PB3)
/PB4: BAR3.6 (A), J2.5, J11.15, U7.22 (PB4)
/PB5: BAR3.5 (A), J2.6, J11.16, U7.23 (PB5)
/PB6: BAR3.4 (A), J2.7, J11.17, U7.24 (PB6)
/PB7: BAR3.3 (A), J2.8, J11.18, U7.25 (PB7)
/PC0: BAR2.4 (A), J3.1, J11.19, U7.14 (PC0)
/PC1: BAR2.3 (A), J3.2, J11.20, U7.15 (PC1)
/PC2: BAR2.2 (A), J3.3, J11.21, U7.16 (PC2)
/PC3: BAR2.1 (A), J3.4, J11.22, U7.17 (PC3)
/PC4: BAR1.10 (A), J3.5, J11.23, U7.13 (PC4)
/PC5: BAR1.9 (A), J3.6, J11.24, U7.12 (PC5)
/PC6: BAR1.8 (A), J3.7, J11.25, U7.11 (PC6)
/PC7: BAR1.7 (A), J3.8, J11.26, U7.10 (PC7)
/PCLK: J10.40, U11.2 (PCLK), U15.9 (CLK0), U15.15 (CLK1), U15.18 (CLK2)
/RESET: J10.38, U1.21 (RESET), U7.35 (RESET), U11.10 (RESET), U12.35 (RESET), U14.5
/SD_CS: J9.1, R10.2, U12.13 (PC4)
/SD_MISO: J9.4, R9.2, U12.21 (PB3)
/SD_MOSI: J9.3, U12.11 (PC6)
/SD_SCK: J9.2, U12.12 (PC5)
/SPK: R8.1, U9.10
/SPK_BZ: BZ1.1 (+), R8.2
/UART_RX: J5.2, R4.2, U12.20 (PB2), U14.3
/UART_TX: J5.1, U12.37 (PA7)
/VOY_DISQ: D1.2 (A), U12.4 (PA0)
/VOY_HD: D2.2 (A), U12.3 (PA1)
/WR_61: U9.1, U9.5, U9.6
/~CS_61: U8.9 (O6), U9.3
/~CS_8253: U8.11 (O4), U15.21 (~CS)
/~CS_8255_2: U8.12 (O3), U12.6 (~CS)
/~CS_8255: U7.6 (~CS), U8.14 (O1)
/~CS_8259: U8.13 (O2), U13.1 (~CS)
/~INTA: J10.35, U1.24 (~INTA), U13.26 (~INTA)
/~OUT2: U9.8, U14.8
/~RD: J10.33, U1.32 (~RD), U4.24 (OE), U6.24 (OE#), U7.5 (~RD), U12.5 (~RD), U13.3 (~RD), U15.22 (~RD)
/~RESET: U14.6, U16.1 (~R), U16.13 (~R)
/~SPK_EN: U9.9, U16.8 (~Q)
/~WR: J10.34, U1.29 (WR), U6.29 (WE#), U7.36 (~WR), U9.2, U9.11, U12.36 (~WR), U13.2 (~WR), U15.23 (~WR)
GND: BZ1.2 (-), C1.2, C2.2, C3.2, C4.2, C5.2, C6.2, C7.2, C8.2, C9.2, C10.2, C11.2, C12.2, C13.2, C14.2, C15.2, C16.2, C17.2, C18.2, C19.2, C20.2, D3.1 (K), J1.10, J2.10, J3.10, J4.4 (GND), J4.SH (Shield), J5.3, J6.2, J6.3, J7.2, J9.6, J10.2, J10.39, J11.2, J12.7, R5.2, R6.2, R7.2, R11.2, R12.2, R13.2, R14.2, R15.2, R16.2, R17.2, RN1.1 (common), RN2.1 (common), RN3.1 (common), RV1.1, SW1.1, U1.1 (GND), U1.17 (NMI), U1.20 (GND), U1.23 (~TEST), U1.31 (HOLD), U2.1 (OE), U2.10 (GND), U3.1 (OE), U3.2 (D0), U3.3 (D1), U3.4 (D2), U3.5 (D3), U3.10 (GND), U4.16 (GND), U5.7 (GND), U6.16 (VSS), U7.7 (GND), U8.8 (GND), U9.7 (GND), U10.1 (VSS), U10.5 (R/W), U10.16 (K), U11.1 (CSYNC), U11.3 (~AEN1), U11.4 (RDY1), U11.6 (RDY2), U11.7 (~AEN2), U11.9 (GND), U11.13 (F/~C)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
unnamed: D1.1 (K), R11.1
unnamed: D2.1 (K), R12.1
unnamed: D3.2 (A), R18.2
unnamed: U1.38 (A16/S3), U3.6 (D4)
unnamed: U1.37 (A17/S4), U3.7 (D5)
unnamed: U1.36 (A18/S5), U3.8 (D6)
unnamed: U1.35 (A19/S6), U3.9 (D7)
unnamed: U4.22 (CE), U5.6
unnamed: U5.3, U5.9
unnamed: U5.5, U5.10, U5.11
unnamed: U5.8, U6.22 (CE#)
unnamed: U8.15 (O0), U9.12
unnamed: U9.13, U10.6 (E)
unnamed: RV1.2, U10.3 (VO)
unnamed: C3.1, U11.17 (X1), Y1.1
unnamed: C2.1, U11.16 (X2), Y1.2
unnamed: C1.1, R1.2, SW1.2, U11.11 (~RES)

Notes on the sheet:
5.33 MHz
Alimentation de U5 (74LS00) et U9 (74LS02)
U1: 8088 ou NEC V20 (uPD70108 / 70108H, CMOS, recommande: sorties compatibles 74HC573)
U7 = 8255 (uPD71055C) sur O1 du 74LS138 : ports 10h-13h 10h = PA, 11h = PB, 12h = PC, 13h = controle (A0-A1) J1-J3 : DEL des ports PA, PB, PC (broche 9 = +5 V, 10 = GND) DEL : 1 kohm en serie (sortie 82C55 ~2,5 mA)
U12 = 2e 8255 (uPD71055C) sur O3 du 74LS138 : ports 30h-33h 30h = PA, 31h = PB, 32h = PC, 33h = controle Clavier (bit-bang, comme Solution-01) : PB0 = horloge, PB1 = donnees (entrees) J4 : clavier USB a repli PS/2 (D+ = horloge, D- = donnees, comme Solution-01, tirages R2/R3 = mode PS/2) J5 UART TT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
U13 = 8259A sur O2 du 74LS138 : ports 20h-21h (comme le PC) INT -> INTR du 8088 (broche 18, detachee de la masse), ~{INTA} <- broche 24 Maitre unique : ~{SP}/~{EN} a +5 V, CAS0-2 libres ; IR0, IR2, IR3, IR5-IR7 libres (masquees par le BIOS) IR1 = clavier (INT 09h) : 74LS14 inverse KBD_CLK -> front 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
U15 = NEC D8253C-2 (8253-2 : horloge 5 MHz max ; symbole 82C54, meme brochage) sur O4 du 74LS138 : ports 40h-43h (comme le PC) CLK0-2 = PCLK du 82C84 (16 MHz / 6 = 2,67 MHz) : 8253-2 ou 8254, pas une 8253 / 8253-5 (2,6 MHz max) GATE0-1 a +5 V ; GATE2 = bit 0 du port 61h (U16) ; OUT0 -> IR0 du 8259 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
BAR1-3 = HDSP-4830 sur U7 (8255, 10h-12h), comme Solution-01 : anode sur la sortie, cathode a la masse par 390 ohms (RN1-3 = 9 resistances SIP10 + R5-R7 pour la 10e DEL). Chaine contigue de 30 DEL : bit 0 = PB0 (BAR3 broche 10) ... PB7, PA0-PA7, PC0-PC7 = bit 23 (BAR1 broche 7) ; BAR1 broches 1-6 l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
Son, comme le PC : U16 (74LS74) = verrou du port 61h (O6 du 74LS138), horloge CLK_61 = OR(~WR, ~CS_61) (U9 A et B) : front montant a la fin de l ecriture. Bit 0 -> GATE2 de la 8253 ; bit 1 -> validation du son. RESET -> 0 (silence). SPK = OUT2 ET bit 1 = NOR(~OUT2, ~SPK_EN) (U9 C, U14 D) -> R8 220 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
J9 = module lecteur microSD (regulateur AMS1117 3,3 V et 74LVC125 a bord) : VCC au +5 V. SPI fait par le 8088 sur U12 (8255, mode 0, mot 82h inchange) : PC4 = CS, PC5 = SCK, PC6 = MOSI (sorties), PB3 = MISO (entree ; 3,3 V suffit au 8255). R9 : MISO au +5 V (sans carte) ; R10 : CS au +5 V (RESET : 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
Voyants d acces aux disques (BIOS 1.7), sur U12, a part du LED Show : D1 = PA0 (VOY_DISQ) : disquettes A:/B: de la carte SD ; D2 = PA1 (VOY_HD) : disque dur C:. Actifs a 1 (PA7 = UART TX reste a 1 au repos) ; 390 ohms comme les bargraphes.
J10 : bus du 8088 (2x20, pas de 2,54 mm)
A0-A19 verrouillees (74HC573), D0-D7, ALE, IO/M, RD#, WR#,
INTA#, INTR, CLK (5,33 MHz), PCLK, RESET
1 = +5 V ; 2 et 39 = GND
J11 : ports du 8255 U7 (10h-13h), en parallele avec J1-J3
PA0-PA7, PB0-PB7, PC0-PC7 ; 1 = +5 V, 2 = GND
J12 : entrees libres du 8259 U13 : IR2, IR3, IR5, IR6, IR7
= INT 0Ah, 0Bh, 0Dh, 0Eh, 0Fh ; tirees a la masse (R13-R17)
demande = front montant tenu jusqu'a INTA# (BIOS : IMR = ECh)
ALIMENTATION : J6 = jack 5 V regule (centre +, 2,1 mm), J7 = bornier +5 V / GND,
C20 = reservoir, D3 = voyant +5 V ; pas de regulateur ni de protection de polarite
DECOUPLAGE : C4-C19 = 100 nF, un par circuit
integre et un au LCD, pres des broches +5 V / GND

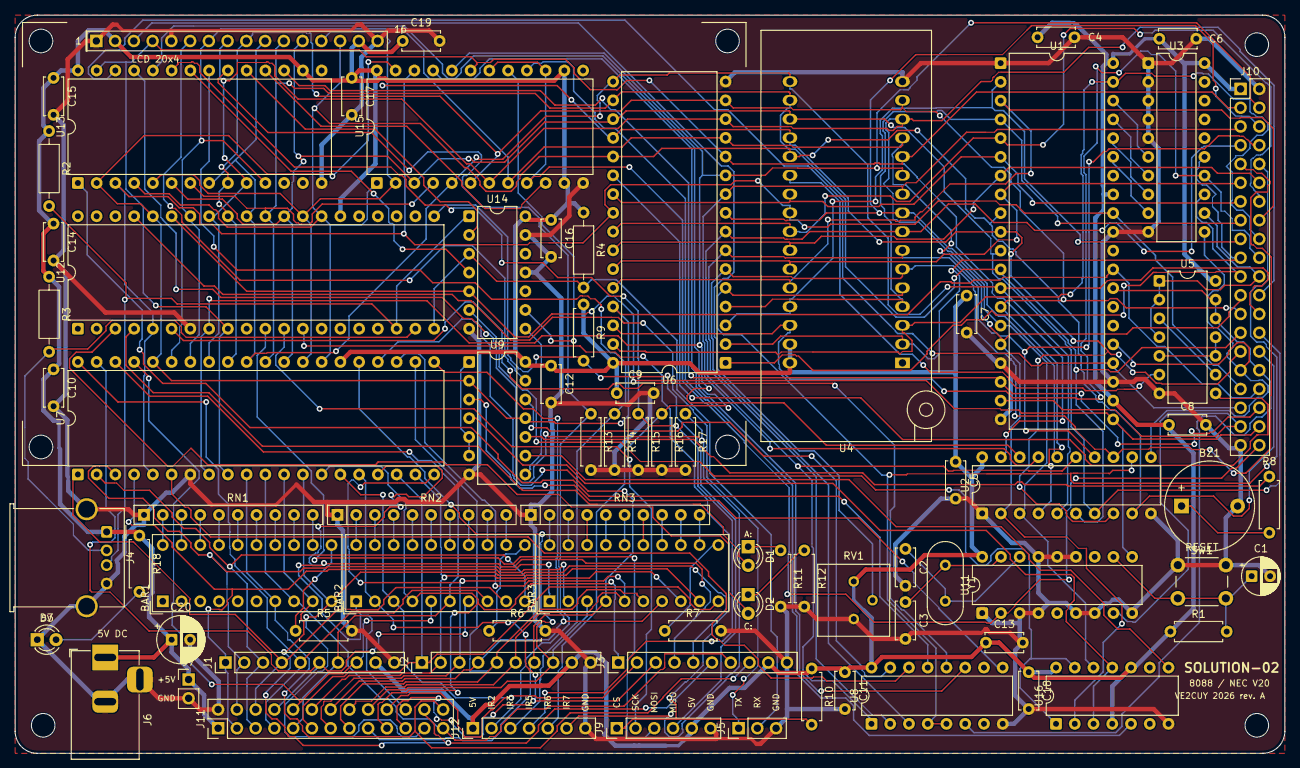
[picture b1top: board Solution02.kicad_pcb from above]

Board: 2 copper layers, 172.0 x 100.0 mm, 81 parts (0 on the bottom side), 142 nets.

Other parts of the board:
H1, H2, H3: M3; MountingHole_3.2mm_M3
